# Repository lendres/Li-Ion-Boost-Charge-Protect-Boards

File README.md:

# Li-Ion-Boost-Charge-Protect-Boards

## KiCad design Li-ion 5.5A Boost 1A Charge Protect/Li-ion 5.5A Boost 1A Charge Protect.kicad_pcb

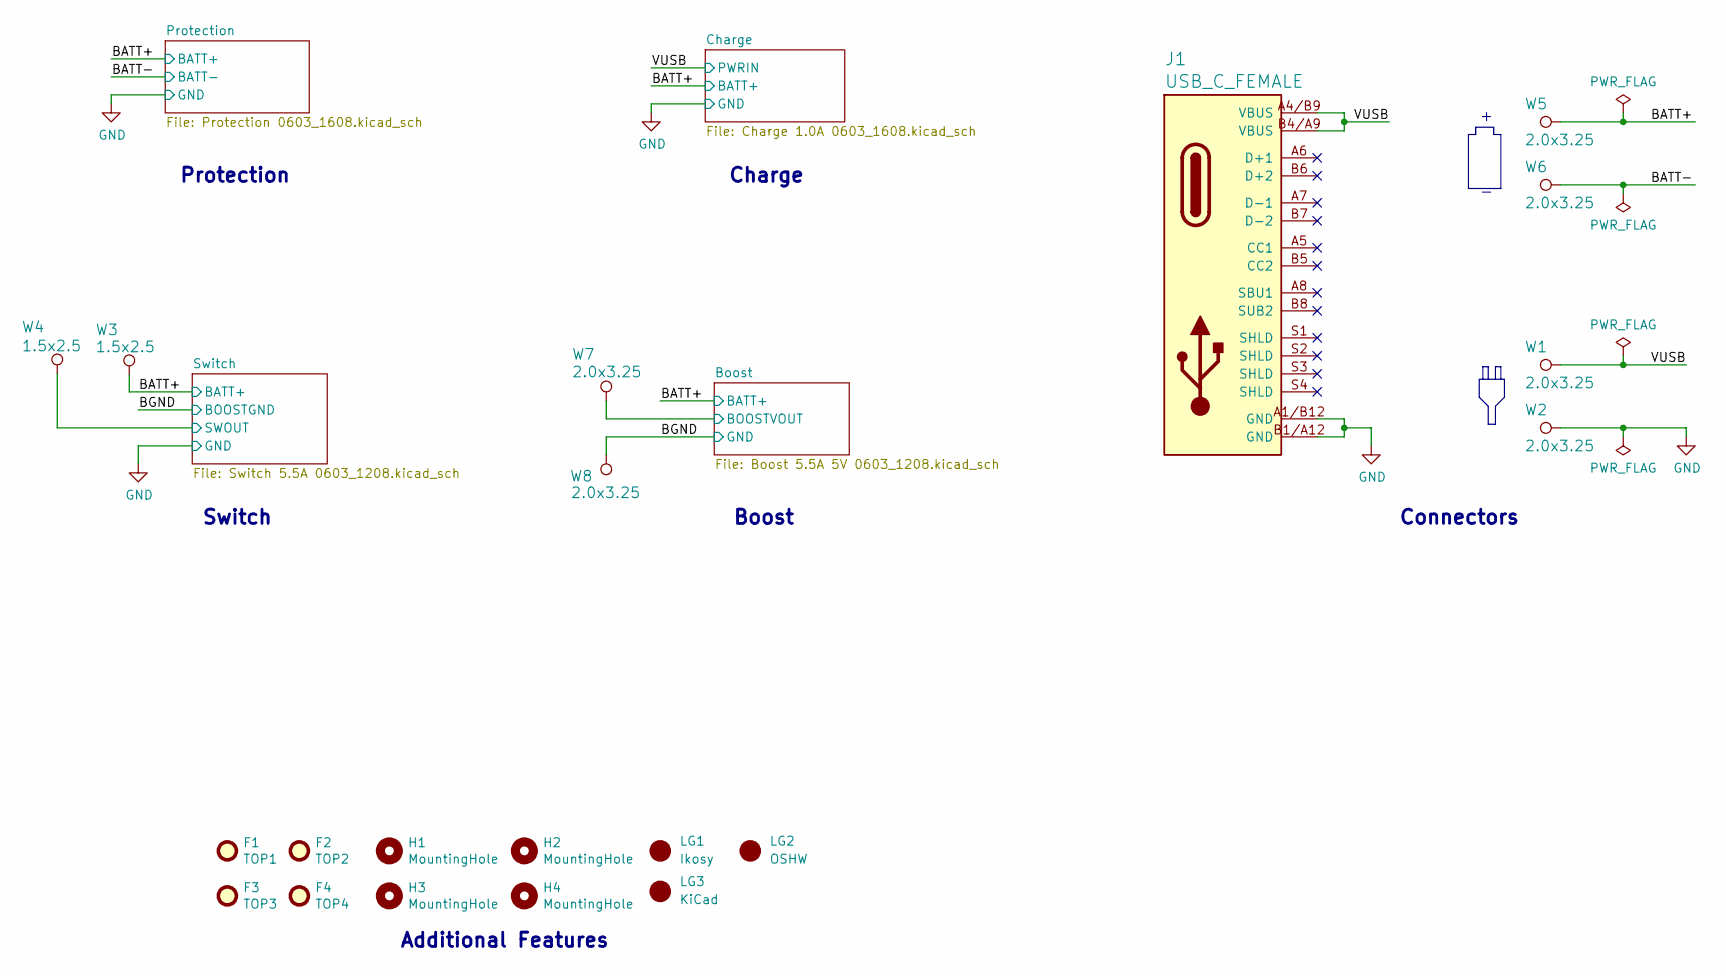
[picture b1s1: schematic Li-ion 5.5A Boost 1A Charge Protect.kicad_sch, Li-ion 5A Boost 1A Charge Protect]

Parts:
F1, F2, F3, F4: Fiducial; Fiducial_1mm_Mask2mm; Manufacturer Part No. None
H1, H2, H3, H4: MountingHole; MountingHole_2.2mm_M2; Manufacturer Part No. None
J1: USB_C_FEMALE; GCT_USB4110-GF-A; Manufacturer Part No. USB4110-GF-A
LG1: Logo; Ikosy-Logo_Type1_10.3x2mm_SilkScreen; Manufacturer Part No. None
LG2: Logo; OSHW-Symbol_3mm_Silkscreen; Manufacturer Part No. None
LG3: Logo; KiCad-Logo3_3mm_SilkScreen; Manufacturer Part No. None
W1, W2, W5, W6, W7, W8: 2.0x3.25; Pad_2.0-3.25_w_TH; Manufacturer Part No. None
W3, W4: 1.5x2.5; Pad_1.5-2.5_w_TH; Manufacturer Part No. None

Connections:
/BATT+: W3.1, W5.1; also elsewhere on the board
/BATT-: W6.1; also elsewhere on the board
/BGND: W8.1; also elsewhere on the board
/Boost/BOOSTVOUT: W7.1; also elsewhere on the board
/Switch/SWOUT: W4.1; also elsewhere on the board
/VUSB: J1.A4/B9 (VBUS), J1.B4/A9 (VBUS), W1.1; also elsewhere on the board
GND: J1.A1/B12 (GND), J1.B1/A12 (GND), W2.1; also elsewhere on the board

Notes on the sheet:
Protection
Switch
Connectors
Additional Features
Charge
Boost

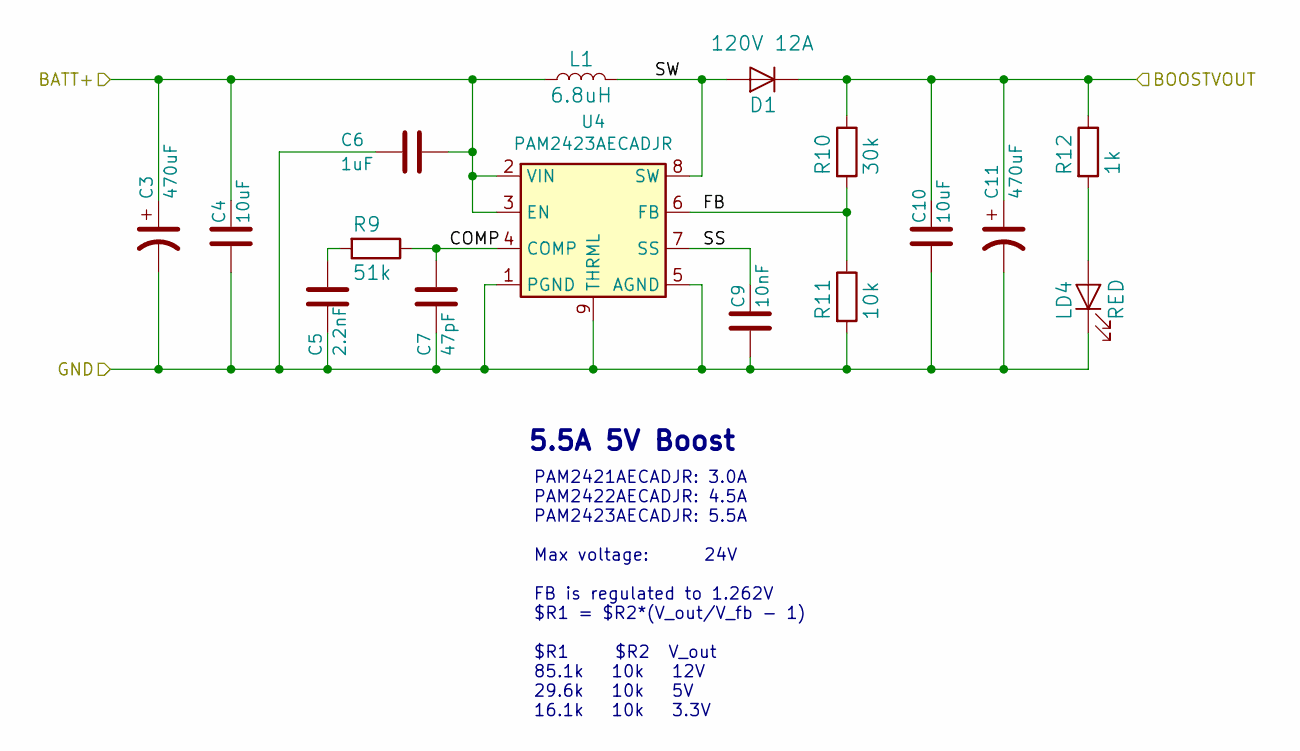
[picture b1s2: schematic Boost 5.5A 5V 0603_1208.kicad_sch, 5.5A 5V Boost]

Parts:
C3, C11: 470uF; CP_Elec_10x10.5; Manufacturer Part No. 25TLV470M10X10.5
C4, C10: 10uF; 0603_1608Metric; Manufacturer Part No. CL10A106KP8NQSC
C5: 2.2nF; 0603_1608Metric; Manufacturer Part No. CL10B222KB8NFNC
C6: 1uF; 0603_1608Metric; Manufacturer Part No. CL10A105KA8NFNC
C7: 47pF; 0603_1608Metric; Manufacturer Part No. CL10C470JB81PNC
C9: 10nF; 0603_1608Metric; Manufacturer Part No. CL10B103KB8NNNL
D1: 120V 12A; NTS12120EMFST1G; Manufacturer Part No. NTS12120EMFST1G
L1: 6.8uH; L_MGV1004; Manufacturer Part No. MGV10046R8M-10
LD4: RED; LED_0805_2012Metric; Manufacturer Part No. 150080RS75000
R9: 51k; 0603_1608Metric; Manufacturer Part No. ESR03EZPF5102
R10: 30k; 0603_1608Metric; Manufacturer Part No. ESR03EZPF3002
R11: 10k; 0603_1608Metric; Manufacturer Part No. ESR03EZPF1002
R12: 1k; 0603_1608Metric; Manufacturer Part No. ESR03EZPF1001
U4: PAM2423AECADJR; Manufacturer Part No. PAM2423AECADJR

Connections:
/BATT+: C3.1, C4.1, C6.1, L1.1, U4.2 (VIN), U4.3 (EN); also elsewhere on the board
/BGND: C3.2, C4.2, C5.2, C6.2, C7.2, C9.2, C10.2, C11.2, LD4.1 (K(N)), R11.2, U4.1 (PGND), U4.5 (AGND), U4.9 (THRML); also elsewhere on the board
/Boost/BOOSTVOUT: C10.1, C11.1, D1.5 (K), D1.5A (K), D1.5B (K), D1.5C (K), D1.5D (K), R10.1, R12.1; also elsewhere on the board
/Boost/COMP: C7.1, R9.1, U4.4 (COMP)
/Boost/FB: R10.2, R11.1, U4.6 (FB)
/Boost/SS: C9.1, U4.7 (SS)
/Boost/SW: D1.1 (A), D1.2 (A), D1.3 (A), L1.2, U4.8 (SW)
unnamed: C5.1, R9.2
unnamed: LD4.2 (A(P)), R12.2

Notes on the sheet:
5.5A 5V Boost
PAM2421AECADJR: 3.0A PAM2422AECADJR: 4.5A PAM2423AECADJR: 5.5A Max voltage: 24V FB is regulated to 1.262V $R1 = $R2*(V_out/V_fb - 1) $R1 $R2 V_out 85.1k 10k 12V 29.6k 10k 5V 16.1k 10k 3.3V

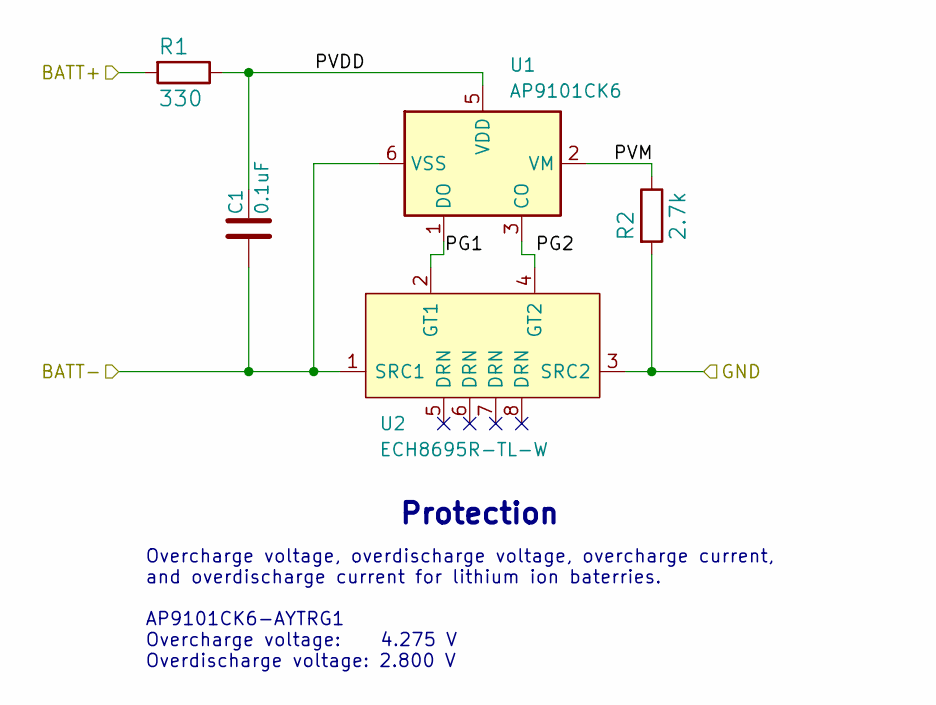
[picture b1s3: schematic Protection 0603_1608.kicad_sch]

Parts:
C1: 0.1uF; 0603_1608Metric; Manufacturer Part No. CL10B104JB8NNNC
R1: 330; 0603_1608Metric; Manufacturer Part No. BUK6D30-40EX
R2: 2.7k; 0603_1608Metric; Manufacturer Part No. ESR03EZPF2701
U1: AP9101CK6; SOT-23-6; Manufacturer Part No. AP9101CK6-AYTRG1
U2: ECH8695R-TL-W; SOT65P280X95-8N; Manufacturer Part No. ECH8695R-TL-W

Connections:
/BATT+: R1.2; also elsewhere on the board
/BATT-: C1.2, U1.6 (VSS), U2.1 (SRC1); also elsewhere on the board
/Protection/PG1: U1.1 (DO), U2.2 (GT1)
/Protection/PG2: U1.3 (CO), U2.4 (GT2)
/Protection/PVDD: C1.1, R1.1, U1.5 (VDD)
/Protection/PVM: R2.1, U1.2 (VM)
GND: R2.2, U2.3 (SRC2); also elsewhere on the board

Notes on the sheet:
Protection
Overcharge voltage, overdischarge voltage, overcharge current, and overdischarge current for lithium ion baterries. AP9101CK6-AYTRG1 Overcharge voltage: 4.275 V Overdischarge voltage: 2.800 V

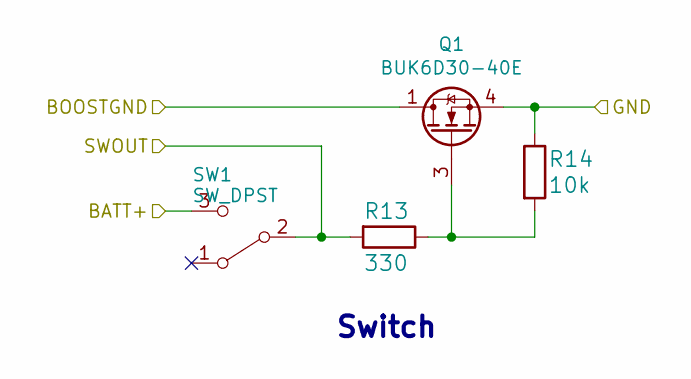
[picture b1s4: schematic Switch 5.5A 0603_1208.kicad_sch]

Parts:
Q1: BUK6D30-40E; BUK6D3040EX; Manufacturer Part No. BUK6D30-40EX
R13: 330; 0603_1608Metric; Manufacturer Part No. BUK6D30-40EX
R14: 10k; 0603_1608Metric; Manufacturer Part No. ESR03EZPF1002
SW1: SW_DPST; CL-SB-22A_Edge; Manufacturer Part No. CL-SB-22A-11T

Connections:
/BATT+: SW1.3 (2), SW1.6 (2); also elsewhere on the board
/BGND: Q1.1 (D), Q1.2 (D), Q1.5 (D), Q1.6 (D), Q1.7 (D); also elsewhere on the board
/Switch/SWOUT: R13.2, SW1.2 (C), SW1.5 (C); also elsewhere on the board
GND: Q1.4 (S), Q1.8 (S), R14.1; also elsewhere on the board
unnamed: Q1.3 (G), R13.1, R14.2
unnamed: SW1.1, SW1.4 (1)

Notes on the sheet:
Switch

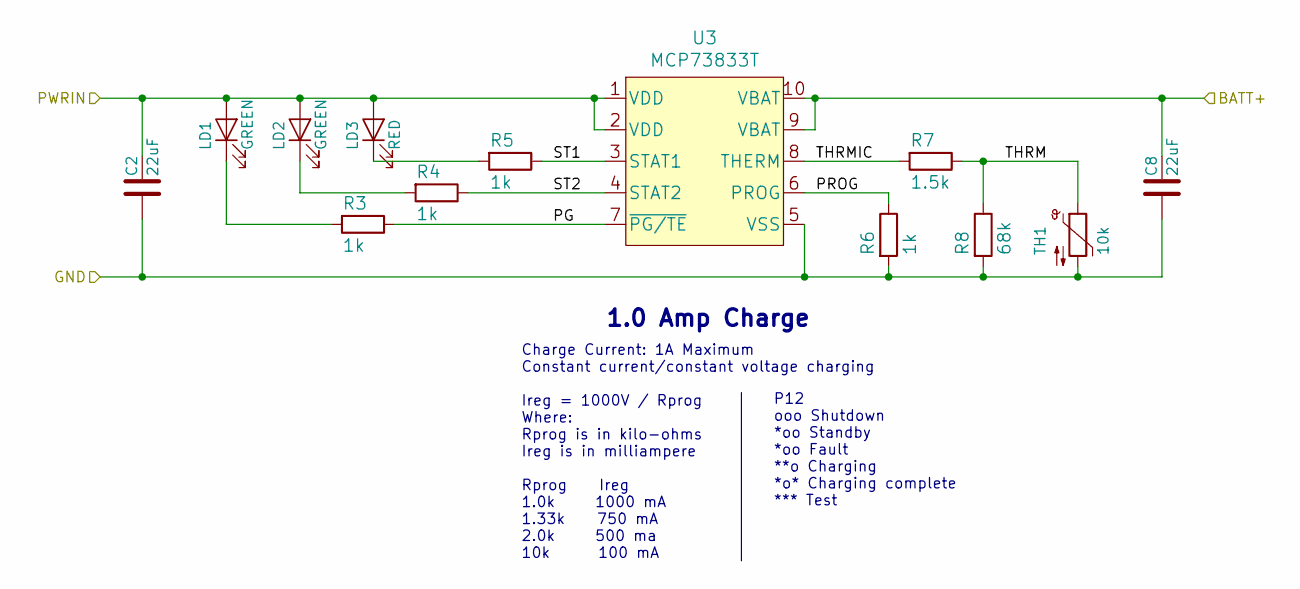
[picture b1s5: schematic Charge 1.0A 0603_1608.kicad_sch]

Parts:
C2, C8: 22uF; 0603_1608Metric; Manufacturer Part No. CL10A226MQ8NRNE
LD1, LD2: GREEN; LED_0805_2012Metric; Manufacturer Part No. 150080VS75000
LD3: RED; LED_0805_2012Metric; Manufacturer Part No. 150080RS75000
R3, R4, R5, R6: 1k; 0603_1608Metric; Manufacturer Part No. ESR03EZPF1001
R7: 1.5k; 0603_1608Metric; Manufacturer Part No. ESR03EZPF1501
R8: 68k; 0603_1608Metric; Manufacturer Part No. ESR03EZPF6802
TH1: 10k; 0603_1608Metric; Manufacturer Part No. NTCG163JH103JT
U3: MCP73833T; MCP73833; Manufacturer Part No. MCP73833T-AMI/UN

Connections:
/BATT+: C8.1, U3.9 (VBAT), U3.10 (VBAT); also elsewhere on the board
/Charge/PG: R3.1, U3.7 (~PG/TE)
/Charge/PROG: R6.1, U3.6 (PROG)
/Charge/ST1: R5.1, U3.3 (STAT1)
/Charge/ST2: R4.1, U3.4 (STAT2)
/Charge/THRM: R7.1, R8.1, TH1.1
/Charge/THRMIC: R7.2, U3.8 (THERM)
/VUSB: C2.1, LD1.2 (A(P)), LD2.2 (A(P)), LD3.2 (A(P)), U3.1 (VDD), U3.2 (VDD); also elsewhere on the board
GND: C2.2, C8.2, R6.2, R8.2, TH1.2, U3.5 (VSS); also elsewhere on the board
unnamed: LD1.1 (K(N)), R3.2
unnamed: LD2.1 (K(N)), R4.2
unnamed: LD3.1 (K(N)), R5.2

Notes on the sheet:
P12 ooo Shutdown *oo Standby *oo Fault **o Charging *o* Charging complete *** Test
1.0 Amp Charge
Charge Current: 1A Maximum Constant current/constant voltage charging Ireg = 1000V / Rprog Where: Rprog is in kilo-ohms Ireg is in milliampere Rprog Ireg 1.0k 1000 mA 1.33k 750 mA 2.0k 500 ma 10k 100 mA

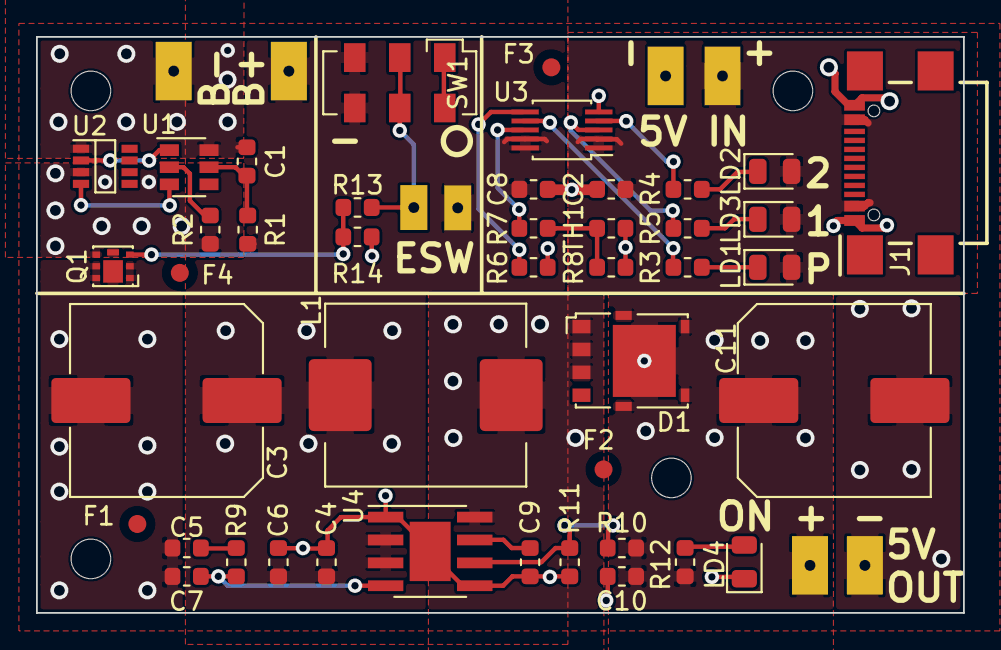
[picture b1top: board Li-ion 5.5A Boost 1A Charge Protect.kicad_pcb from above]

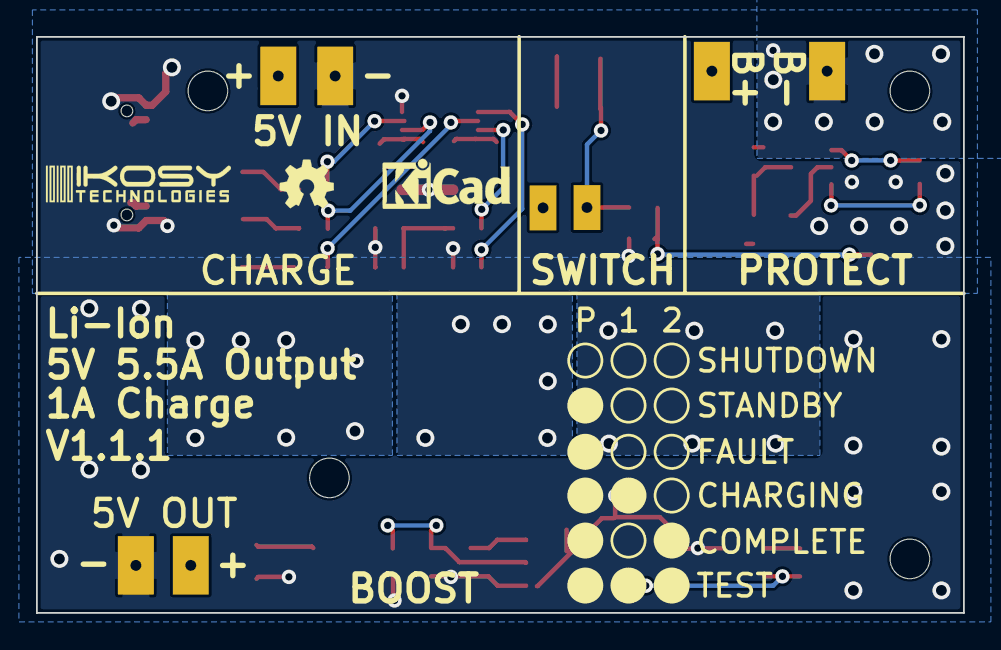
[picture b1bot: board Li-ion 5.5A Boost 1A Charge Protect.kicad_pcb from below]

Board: 2 copper layers, 51.5 x 32.0 mm, 58 parts (3 on the bottom side), 28 nets.

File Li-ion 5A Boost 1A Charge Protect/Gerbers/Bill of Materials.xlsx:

Source: | S:\Projects and Builds\2020-05 Li-Ion Power Boards\Li-Ion-Boost-Charge-Protect-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
Date: | 44073.904999999999
Tool: | Eeschema (5.1.5)-3
Generator: | F:\Program Files\KiCad\bin\scripting\plugins/bom_csv_grouped_by_value.py
Component Count: | 44
Collated Components:
Item | Qty | Ref | Value | LibPart | Footprint | Datasheet | Description | Manufacturer Name | Manufacturer Part No. | Source | Source Part No.
1 | 1 | C1 | 0.1uF | Frequently_Used_LE:C | Li-ion:0805_2012Metric_HandSolder | https://media.digikey.com/pdf/Data%20Sheets/Samsung%20PDFs/C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 | 0.1ÂµF Â±20% 50V Ceramic Capacitor X7R 0805 (2012 Metric) | Samsung Electro-Mechanics | CL21B104MBCNNNC | Digikey | 1276-2450-1-ND
2 | 2 | C2, C8 | 22uF | Frequently_Used_LE:C | Li-ion:0805_2012Metric_HandSolder | https://media.digikey.com/pdf/Data%20Sheets/Samsung%20PDFs/C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 | 22ÂµF Â±10% 6.3V Ceramic Capacitor X5R 0805 (2012 Metric) | Samsung Electro-Mechanics | CL21A226KQCLRNC | Digikey | 1276-6687-1-ND
3 | 2 | C3, C11 | 470uF | Frequently_Used_LE:CP1 | Li-ion:UCD1E471MNL1GS | https://www.nichicon.co.jp/english/products/pdfs/e-ucd.pdf | 470ÂµF 25V Aluminum Electrolytic Capacitors Radial, Can - SMD | Nichicon | UCD1E471MNL1GS | Digikey | 493-6386-1-ND
4 | 2 | C4, C10 | 10uF | Frequently_Used_LE:C | Li-ion:0805_2012Metric_HandSolder | https://media.digikey.com/pdf/Data%20Sheets/Samsung%20PDFs/C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 | 10ÂµF Â±10% 6.3V Ceramic Capacitor X5R 0805 (2012 Metric) | Samsung Electro-Mechanics | CL21A106KQCLRNC | Digikey | 1276-2405-1-ND
5 | 1 | C5 | 2.2nF | Frequently_Used_LE:C | Li-ion:0805_2012Metric_HandSolder | https://media.digikey.com/pdf/Data%20Sheets/Samsung%20PDFs/C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 | 2200pF Â±10% 50V Ceramic Capacitor X7R 0805 (2012 Metric) | Samsung Electro-Mechanics | CL21B222KBANNNC | Digikey | 1276-1171-1-ND
6 | 1 | C6 | 1uF | Frequently_Used_LE:C | Li-ion:0805_2012Metric_HandSolder | https://media.digikey.com/pdf/Data%20Sheets/Samsung%20PDFs/C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 | 1ÂµF Â±10% 16V Ceramic Capacitor X7R 0805 (2012 Metric) | Samsung Electro-Mechanics | CL21B105KOFNNWE | Digikey | 1276-2931-1-ND
7 | 1 | C7 | 47pF | Frequently_Used_LE:C | Li-ion:0805_2012Metric_HandSolder | https://media.digikey.com/pdf/Data%20Sheets/Samsung%20PDFs/C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 | 47pF Â±5% 50V Ceramic Capacitor C0G, NP0 0805 (2012 Metric) | Samsung Electro-Mechanics | CL21C470JBANNNC | Digikey | 1276-1156-1-ND
8 | 1 | C9 | 10nF | Frequently_Used_LE:C | Li-ion:0805_2012Metric_HandSolder | https://media.digikey.com/pdf/Data%20Sheets/Samsung%20PDFs/C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 | 10000pF Â±10% 50V Ceramic Capacitor X7R 0805 (2012 Metric) | Samsung Electro-Mechanics | CL21B103KBANNNC | Digikey | 1276-1015-1-ND
9 | 1 | D1 | NTS12120EMFST1G | Li-ion_LE:D_NTS12120EMFST1G | Li-ion:NTS12120EMFST1G | https://www.onsemi.com/pub/Collateral/NTS12120EMFS-D.PDF | Diode Schottky 120V 12A | ON Semiconductor | NTS12120EMFST1G | Digikey | NTS12120EMFST1GOSCT-ND
10 | 1 | J1 | USB_C_FEMALE | Connector_LE:USB_C_Plug_USB2.0 | Li-ion:GCT_USB4110-GF-A | https://gct.co/files/drawings/usb4110.pdf | USB-C 2.0 Female SMD Connector | GCT | USB4110-GF-A | Digikey | 2073-USB4110-GF-A-1-ND
11 | 1 | L1 | 6.8uH | Frequently_Used_LE:L | Li-ion:L_MGV1004 | https://media.digikey.com/pdf/Data%20Sheets/Steward%20PDFs/M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 | 6.8ÂµH Shielded Molded Inductor 8A 23.3mOhm | Laird-Signal Integrity Products | MGV10046R8M-10 | Digikey | 240-2938-1-ND
12 | 2 | LD1, LD2 | GREEN | Frequently_Used_LE:LED | Li-ion:LED_0805_2012Metric_HandSolder | https://www.we-online.de/katalog/datasheet/150080VS75000.pdf | Green 570nm LED Indication - Discrete 2V 0805 (2012 Metric) | WÃ¼rth Elektronik | 150080VS75000 | Digikey | 732-4986-1-ND
13 | 2 | LD3, LD4 | RED | Frequently_Used_LE:LED | Li-ion:LED_0805_2012Metric_HandSolder | https://www.we-online.de/katalog/datasheet/150080RS75000.pdf | Red 625nm LED Indication - Discrete 2V 0805 (2012 Metric) | WÃ¼rth Elektronik | 150080RS75000 | Digikey | 732-4984-1-ND
14 | 1 | R1 | 330 | Frequently_Used_LE:R | Li-ion:0805_2012Metric_HandSolder | http://www.koaspeer.com/pdfs/RK73H.pdf | 330 Ohms Â±1% 0.25W, 1/4W Chip Resistor 1206 (3216 Metric) | KOA Speer Electronics, Inc. | RK73H2ATTD3300F | Digikey | 2019-RK73H2ATTD3300FCT-ND
15 | 1 | R2 | 2.7k | Frequently_Used_LE:R | Li-ion:0805_2012Metric_HandSolder | http://www.koaspeer.com/pdfs/RK73H.pdf | 2.7 kOhms Â±1% 0.25W, 1/4W Chip Resistor 1206 (3216 Metric) | KOA Speer Electronics, Inc. | RK73H2ATTD2701F | Digikey | 2019-RK73H2ATTD2701FCT-ND
16 | 5 | R3, R4, R5, R6, R12 | 1k | Frequently_Used_LE:R | Li-ion:0805_2012Metric_HandSolder | http://www.koaspeer.com/pdfs/RK73H.pdf | 1 kOhms Â±1% 0.25W, 1/4W Chip Resistor 1206 (3216 Metric) | KOA Speer Electronics, Inc. | RK73H2ATTD1001F | Digikey | 2019-RK73H2ATTD1001FCT-ND
17 | 1 | R7 | 1.54k | Frequently_Used_LE:R | Li-ion:0805_2012Metric_HandSolder | http://www.koaspeer.com/pdfs/RK73H.pdf | 1.54 kOhms Â±1% 0.25W, 1/4W Chip Resistor 1206 (3216 Metric) | KOA Speer Electronics, Inc. | RK73H2ATTD1541F | Digikey | 2019-RK73H2ATTD1541FCT-ND
18 | 1 | R8 | 69.8k | Frequently_Used_LE:R | Li-ion:0805_2012Metric_HandSolder | http://www.koaspeer.com/pdfs/RK73H.pdf | 69.8 kOhms Â±1% 0.25W, 1/4W Chip Resistor 1206 (3216 Metric) | KOA Speer Electronics, Inc. | RK73H2ATTD6982F | Digikey | 2019-RK73H2ATTD6982FCT-ND
19 | 1 | R9 | 51k | Frequently_Used_LE:R | Li-ion:0805_2012Metric_HandSolder | http://www.koaspeer.com/pdfs/RK73H.pdf | 51 kOhms Â±1% 0.25W, 1/4W Chip Resistor 1206 (3216 Metric) | KOA Speer Electronics, Inc. | RK73H2ATTD5102F | Digikey | 2019-RK73H2ATTD5102FCT-ND
20 | 1 | R10 | 30k | Frequently_Used_LE:R | Li-ion:0805_2012Metric_HandSolder | http://www.koaspeer.com/pdfs/RK73H.pdf | 30 kOhms Â±1% 0.25W, 1/4W Chip Resistor 1206 (3216 Metric) | KOA Speer Electronics, Inc. | RK73H2ATTD3002F | Digikey | 2019-RK73H2ATTD3002FCT-ND
21 | 1 | R11 | 10k | Frequently_Used_LE:R | Li-ion:0805_2012Metric_HandSolder | http://www.koaspeer.com/pdfs/RK73H.pdf | 10 kOhms Â±1% 0.25W, 1/4W Chip Resistor 1206 (3216 Metric) | KOA Speer Electronics, Inc. | RK73H2ATTD1002F | Digikey | 2019-RK73H2ATTD1002FCT-ND
22 | 1 | SW1 | SW_SPST | Frequently_Used_LE:SW_SPST | Li-ion:GF1230054 | https://media.digikey.com/pdf/Data%20Sheets/CW%20Industries%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 | Slide Switch SPST Through Hole 8.5A 125V | CW Industries | GF-123-0054 | Digikey | CWI333-ND
23 | 1 | TH1 | 10k | Li_Ion_LE:Thermistor_NTC | Li-ion:0805_2012Metric_HandSolder | https://product.tdk.com/info/en/catalog/datasheets/503021/tp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 | NTC Thermistor 10k | TDK Corporation | NTCG203NH103JT1 | Digikey | 445-175460-1-ND
24 | 1 | U1 | AP9101CK6 | Li_Ion_LE:AP9101CK6 | Li-ion:SOT-23-6 | https://www.diodes.com/assets/Datasheets/AP9101C.pdf | Protection IC | Diodes Incorporated | AP9101CK6-AYTRG1 | Digikey | AP9101CK6-AYTRG1DICT-ND
25 | 1 | U2 | ECH8695R-TL-W | Li_Ion_LE:ECH8695R-TL-W_Gates_on_Top | Li-ion:SOT65P280X95-8N | https://www.onsemi.com/pub/Collateral/ECH8695R-D.PDF | Mosfet Array 2 N-Channel (Dual) Common Drain 24V 11A 1.4W | ON Semiconductor | ECH8695R-TL-W | Digikey | ECH8695R-TL-WOSCT-ND
26 | 1 | U3 | MCP73833T | Li_Ion_LE:MCP73833T | Li-ion:MCP73833 | http://ww1.microchip.com/downloads/en/DeviceDoc/22005b.pdf | Charger IC | Microchip Technology | MCP73833T-AMI/UN | Digikey | MCP73833T-AMI/UNCT-ND
27 | 1 | U4 | PAM2423AECADJR | Li_Ion_LE:PAM2423AECADJR | Li-ion:PAM2423AECADJR | https://media.digikey.com/pdf/Data%20Sheets/Diodes%20PDFs/PAM2421,22,23.pdf | Boost Switching Regulator IC | Diodes Incorporated | PAM2423AECADJR | Digikey | PAM2423AECADJRDICT-ND
28 | 8 | W1, W2, W3, W4, W5, W6, W7, W8 | 2.5x5.0 | Frequently_Used_LE:TestPoint_1 | Li-ion:Pad_3.0-5.0_w_TH | None | Wire solder point | None | None | None | None

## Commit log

2020-08-20 Standarizing libraries
2020-10-01 Library updates
2021-04-21 Updates after first build, intermediate check in
2021-04-24 Version 1.1 updates
2021-04-25 Version 1.1 updates
    Version 1.1 updates
2021-04-25 Before moving protection IC
2021-04-25 Before reversing mosfet and protection IC
2021-04-26 Near complete version 1.1.0
2021-04-29 Renaming 5A to 5.5A
2021-04-30 As submitted for manufacturing
2021-05-04 Component extraction
2021-06-24 House keeping updates.
2021-07-07 Fixed origin for exported file formats.
2021-07-23 Fixed position on diode.
    Fixed position on diode.
2021-07-28 Updates for footprint corrections.
2021-07-28 Rearrange schematic fields, fix 3D view
2021-07-28 Update version text
2021-09-17 Fix 3D model on inductor
2021-11-19 Conversion to KiCad version 6.0
